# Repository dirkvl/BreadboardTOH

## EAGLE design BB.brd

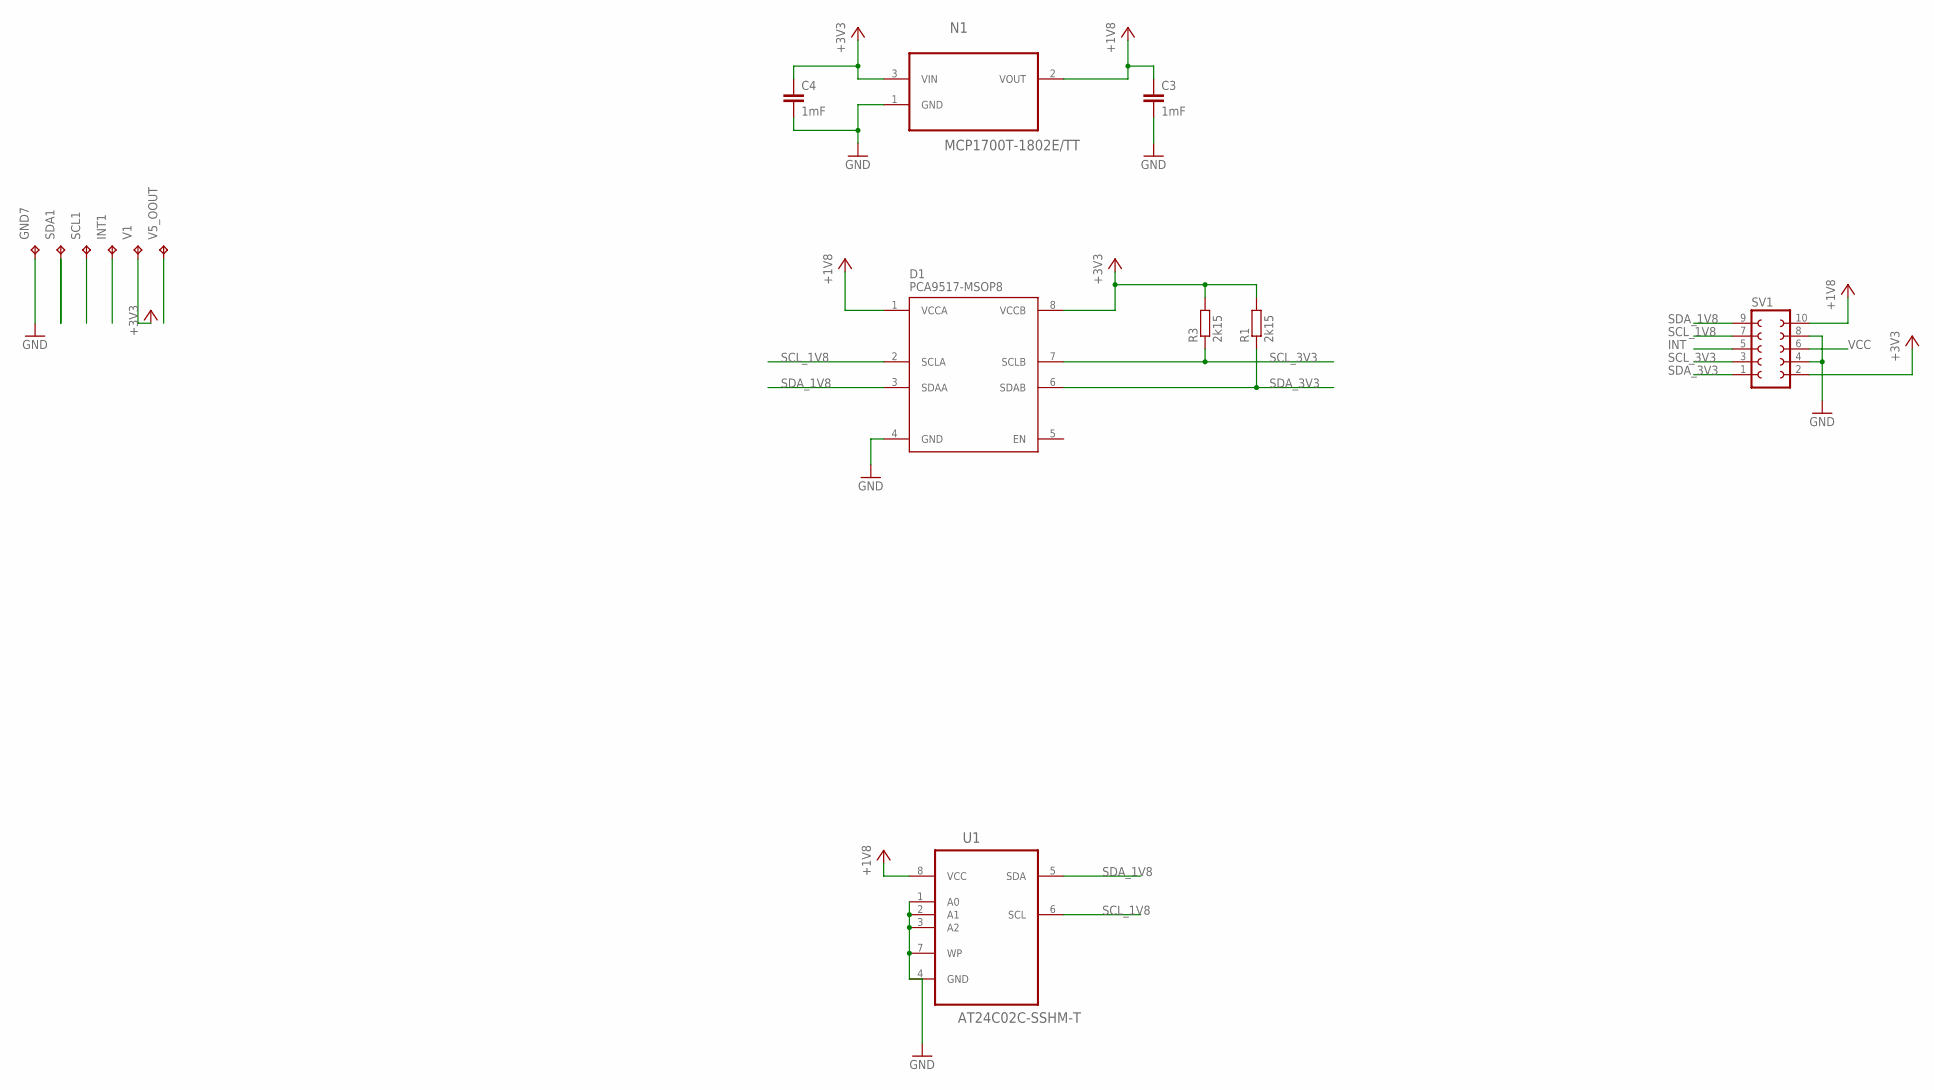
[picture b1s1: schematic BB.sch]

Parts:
C3, C4: 1mF; C1206
D1: PCA9517-MSOP8; SOP65P490X110-8N
GND7: TPTP20SQ; TP20SQ
INT1: TPTP20SQ; TP20SQ
N1: MCP1700T-1802E/TT; SOT95P237X112-3N
R1, R3: 2k15; R1206
SCL1: TPTP20SQ; TP20SQ
SDA1: TPTP20SQ; TP20SQ
SV1: FE05-2
U1: AT24C02C-SSHM-T; SOIC127P600X175-8N
V1, V5_OOUT: TPTP20SQ; TP20SQ

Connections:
+1V8: C3.1, D1.1 (VCCA), N1.2 (VOUT), SV1.10, U1.8 (VCC)
+3V3: C4.1, D1.8 (VCCB), N1.3 (VIN), R1.2, R3.2, SV1.2, V1.TP
GND: C3.2, C4.2, D1.4 (GND), GND7.TP, N1.1 (GND), SV1.4, SV1.8, U1.1 (A0), U1.2 (A1), U1.3 (A2), U1.4 (GND), U1.7 (WP)
INT: INT1.TP, SV1.5
SCL_1V8: D1.2 (SCLA), SCL1.TP, SV1.7, U1.6 (SCL)
SCL_3V3: D1.7 (SCLB), R3.1, SV1.3
SDA_1V8: D1.3 (SDAA), SDA1.TP, SV1.9, U1.5 (SDA)
SDA_3V3: D1.6 (SDAB), R1.1, SV1.1
VCC: SV1.6, V5_OOUT.TP

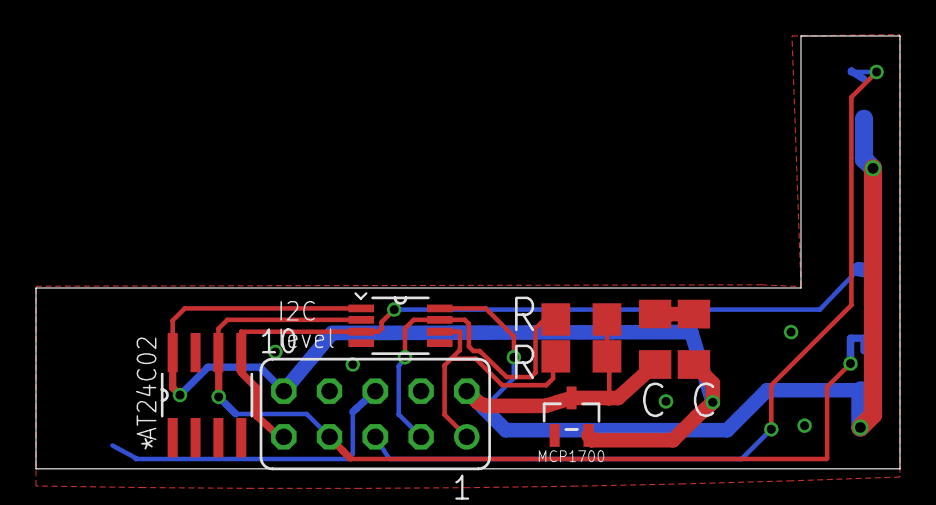
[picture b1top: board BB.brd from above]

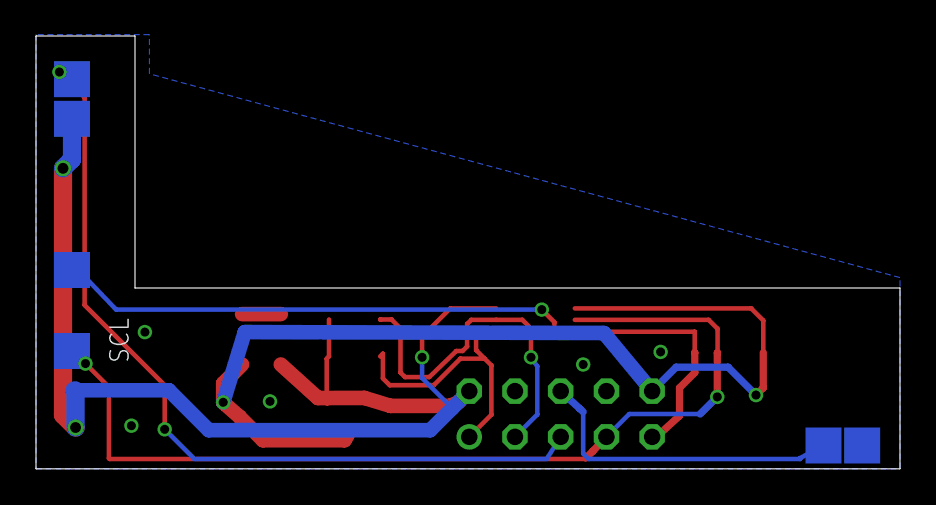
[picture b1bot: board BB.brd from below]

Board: 2 copper layers, 48.0 x 24.0 mm, 14 parts (6 on the bottom side), 9 nets.

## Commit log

2015-08-20 files
